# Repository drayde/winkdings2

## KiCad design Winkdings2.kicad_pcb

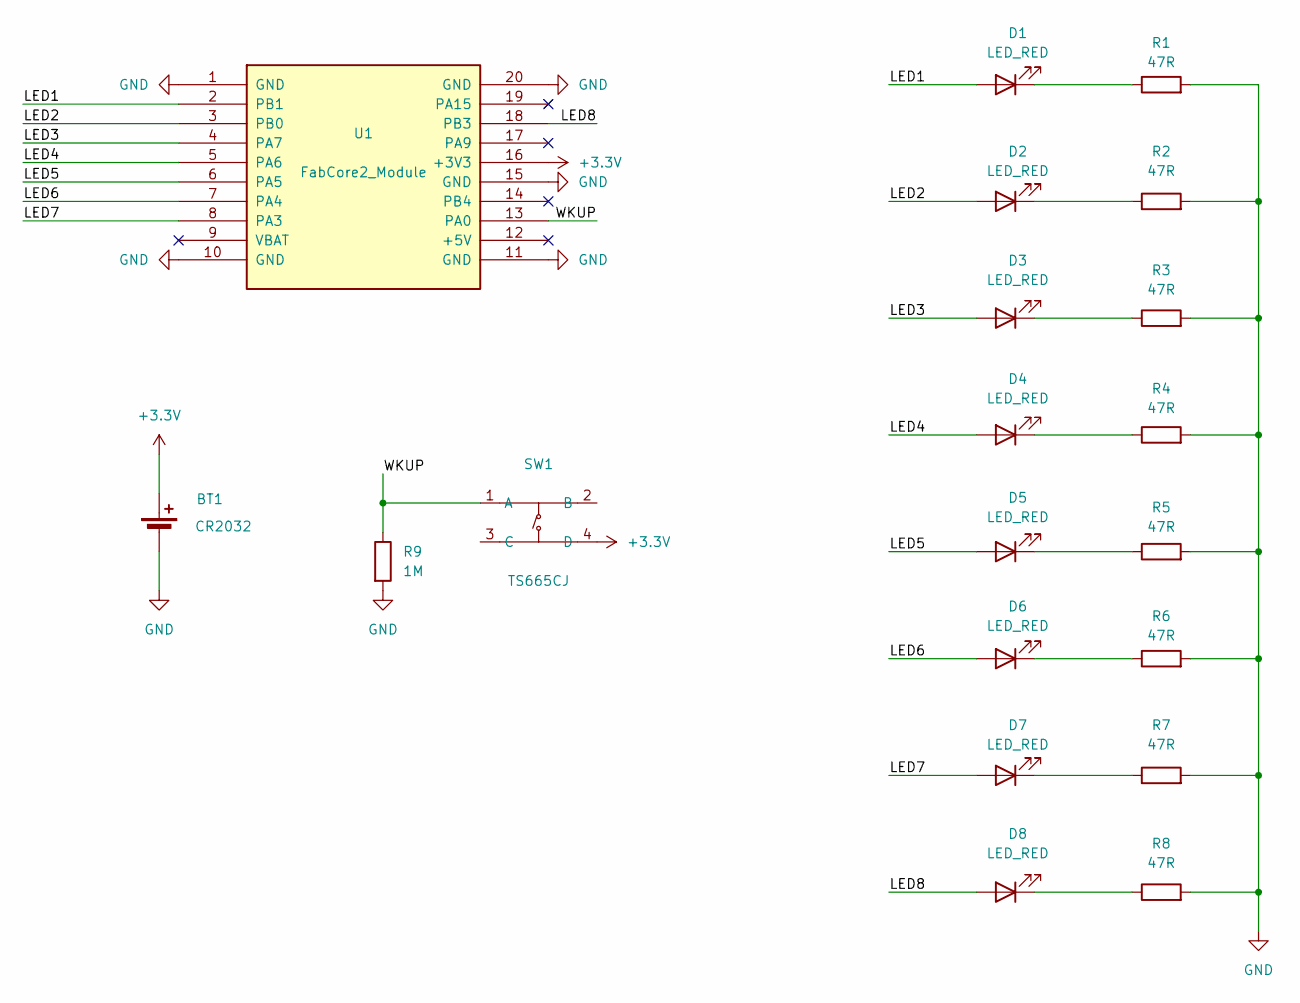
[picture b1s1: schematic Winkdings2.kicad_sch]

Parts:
BT1: CR2032; MYOUNG_BS-02-A1AJ010
D1, D2, D3, D4, D5, D6, D7, D8: LED_RED; LED_D5.0mm
R1, R2, R3, R4, R5, R6, R7, R8: 47R; R_Axial_DIN0207_L6.3mm_D2.5mm_P10.16mm_Horizontal
R9: 1M; R_Axial_DIN0207_L6.3mm_D2.5mm_P10.16mm_Horizontal
SW1: TS665CJ; SW-TH_4P-L6.0-W6.0-P4.50-LS6.5; LCSC Part C393938
U1: FabCore2_Module; FabCore2_Module_2x10_P2.54mm_Row15.24mm

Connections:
+3.3V: BT1.1 (+), SW1.4 (D), U1.16 (+3V3)
/LED1: D1.2 (A), U1.2 (PB1)
/LED2: D2.2 (A), U1.3 (PB0)
/LED3: D3.2 (A), U1.4 (PA7)
/LED4: D4.2 (A), U1.5 (PA6)
/LED5: D5.2 (A), U1.6 (PA5)
/LED6: D6.2 (A), U1.7 (PA4)
/LED7: D7.2 (A), U1.8 (PA3)
/LED8: D8.2 (A), U1.18 (PB3)
/WKUP: R9.1, SW1.1 (A), U1.13 (PA0)
GND: BT1.2 (-), R1.2, R2.2, R3.2, R4.2, R5.2, R6.2, R7.2, R8.2, R9.2, U1.1 (GND), U1.10 (GND), U1.11 (GND), U1.15 (GND), U1.20 (GND)
unnamed: D1.1 (K), R1.1
unnamed: D2.1 (K), R2.1
unnamed: D3.1 (K), R3.1
unnamed: D4.1 (K), R4.1
unnamed: D5.1 (K), R5.1
unnamed: D6.1 (K), R6.1
unnamed: D7.1 (K), R7.1
unnamed: D8.1 (K), R8.1

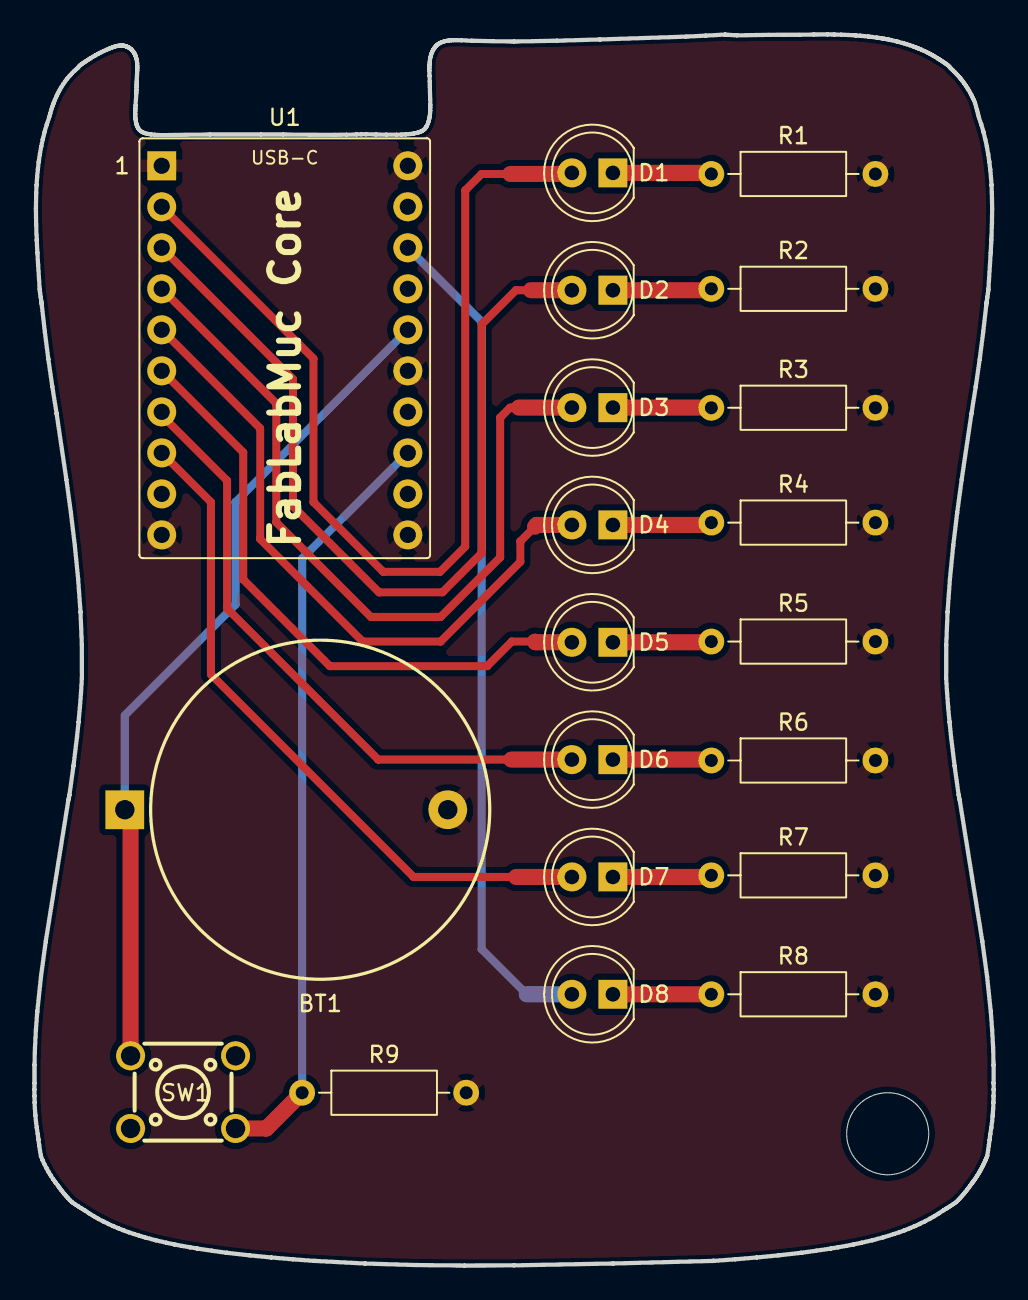
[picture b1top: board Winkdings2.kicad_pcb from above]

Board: 2 copper layers, 59.4 x 76.2 mm, 20 parts (0 on the bottom side), 19 nets.

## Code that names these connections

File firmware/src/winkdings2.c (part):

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 * winkdings2 for CH32V203G6 — POV display: scans user patterns across
 * 8 LEDs, one column at a time at 400 Hz.
 *
 * Button on PA0 (external pulldown, also the WKUP pin):
 *   - press            -> wake from standby / next pattern (wraps)
 *   - hold 2 s         -> USB programming mode (Larson scanner)
 *   - idle 30 s        -> standby
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#define RCC_IOPBEN      (1u << 3)
#define RCC_PWREN       (1u << 28)          /* APB1 */

/* AFIO remap: PB3 is a JTAG pin after reset; SWJ_CFG = 010 keeps
 * SWD enabled and frees PB3/PB4/PA15 for GPIO. */
#define AFIO_PCFR1       (*(volatile uint32_t *)0x40010004u)
#define AFIO_SWJ_CFG     (0x7u << 24)
#define AFIO_SWJ_JTAGDIS (0x2u << 24)
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#define PFIC_SLEEPDEEP  (1u << 2)

/* LED order, pattern bit -> pin (same as heart.c):
 *   LED1 bit0 -> PB1   LED2 bit1 -> PB0   LED8 bit7 -> PB3
 *   LED3 bit2 -> PA7   LED4 bit3 -> PA6   LED5 bit4 -> PA5
 *   LED6 bit5 -> PA4   LED7 bit6 -> PA3
 */
#define GPIOA_LED_MASK  0xF8u           /* PA3..PA7 */
#define GPIOB_LED_MASK  0x0Bu           /* PB0, PB1, PB3 */

/* Timing: the column step is the software tick (~2.5 ms). */
#define DEB_TICKS       8u              /* ~20 ms debounce        */
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
static void show_column(uint8_t col)
{
    uint32_t pa = (col & 0x40u) >> 3  /* bit6 -> PA3 */
                | (col & 0x20u) >> 1  /* bit5 -> PA4 */
                | (col & 0x10u) << 1  /* bit4 -> PA5 */
                | (col & 0x08u) << 3  /* bit3 -> PA6 */
                | (col & 0x04u) << 5; /* bit2 -> PA7 */
    uint32_t pb = (col & 0x01u) << 1  /* bit0 -> PB1 */
                | (col & 0x02u) >> 1  /* bit1 -> PB0 */
                | (col & 0x80u) >> 4; /* bit7 -> PB3 */
    GPIOA_BSHR = pa | ((GPIOA_LED_MASK & ~pa) << 16);
    GPIOB_BSHR = pb | ((GPIOB_LED_MASK & ~pb) << 16);
}
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
/* Single lit LED bouncing 0..7, PB5 blinking in step. Runs for at
 * least `ticks` column-steps, then exits at the end of a full
 * 0->7->0 sweep.  The button is ignored — PA0 floats when no
 * external pulldown is fitted and would abort the sweep early. */
static void larson(uint32_t ticks, uint32_t cdly)
{
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    RCC_APB1PCENR |= RCC_PWREN;
    PWR_CTLR |= PWR_PDDS;           /* standby, not stop           */
    PWR_CTLR |= PWR_CWUF;           /* clear wakeup flag           */
    PWR_CSR  |= PWR_EWUP;           /* PA0/WKUP rising edge wakes  */
    PFIC_SCTLR |= PFIC_SLEEPDEEP;
    __asm__ volatile ("wfi");
    /* STANDBY_RST=1: standby exit does NOT reset — execution resumes
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
int main(void)
{
    /* Still on 8 MHz HSI out of reset. GPIOA (PA3..PA7) + GPIOB
     * (PB0/PB1/PB3 + PB5 blink) LED outputs, push-pull 50 MHz;
     * PA0 input float. */
    RCC_APB2PCENR |= RCC_AFIOEN | RCC_IOPAEN | RCC_IOPBEN;
    AFIO_PCFR1 = (AFIO_PCFR1 & ~AFIO_SWJ_CFG) | AFIO_SWJ_JTAGDIS;
    GPIOA_CFGLR = (GPIOA_CFGLR & ~(0xFFFFF000u | 0xFu))
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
